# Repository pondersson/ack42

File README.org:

* ACK42

[[file:img/ack42.jpg]]

ACK42 is a DIY sandwich-style keyboard with 42 keys inspired by [[https://zealot.hu/absolem/][Absolem]], [[https://github.com/foostan/crkbd][Corne]] and [[https://blog.splitkb.com/introducing-the-kyria/][Kyria]]. The first prototypes were assembled in September 2020 and they have miraculously survived daily use since then.

This repository is a dump of the artifacts left over from the creation process. Things might be broken, so take this not as a finished product ready to be sent off for manufacturing, but rather as a documented example of one way of creating a keyboard.

I briefly entertained the idea of skipping a PCB and instead 3D-printing wire channels and hand-wiring Kailh hotswap sockets (see [[#gallery][Gallery]]). In the end I went the PCB route and that was a good decision in hindsight. It made assembly much easier and I ended up making 4 versions of the keyboard: 2 MX hotswap versions and 2 Choc low-profile versions, 3 of which I still use regularly, some daily.

** Process (rough)

1) CAD top plate, spending countless hours shifting switch positions around a few millimeters at a time and 3D-printing prototypes until things feel just right
2) CAD everything else: bottom plate, screw holes, MCU cutout and cover
3) Dump top plate to a KiCad-friendly format so the outline and switch positions can be used during PCB design
4) Add all PCB components into KiCad, connect them in the electric schematic and then on the PCB
5) Import top plate into KiCad and painstakingly rotate and position all switch footprints so they're lined up with the top plate
6) Add some art to give the PCB some flair
7) Export Gerber files from KiCad and send them off to the manufacturer
8) Export all necessary SVG files from OpenSCAD, tile them neatly in a single SVG file that represent an acrylic sheet and send it off for laser cutting
9) Order all other necessary components (see [[#materials][Materials]])
10) Wait for parts to arrive
11) Assemble the keyboard(s)
   
**  Materials

All parts required to assemble a single ACK42 keyboard (MX variant):

- 1 ACK42 PCB
- 1 Elite-C microcontroller with pins + stand-offs
- 8 M3 12 mm screws
- 8 M3 cap nuts
- 2 M2 screws
- 2 M2 stand-offs
- 64 0.5 mm washers (or equivalent)
- 42 Kailh hotswap sockets
- 42 through-hole diodes
- 42 MX-style switches
- 42 Keycaps
   
** Gallery

[[file:img/ack42_triangle.jpg]]
[[file:img/ack42_little_pilot.jpg]]
[[file:img/ack42_space_cadet.jpg]]
[[file:img/ack42_low_profile.jpg]]

[[file:img/draft_edge.png]]
[[file:img/draft_handwire.png]]

[[file:img/pcb_render_0.png]]
[[file:img/pcb_render_1.jpg]]
[[file:img/pcb_render_2.png]]
[[file:img/pcb.jpg]]

** License
[[file:LICENSE]] © Pontus Andersson

The KiCad components were taken from the following repositories and their licenses can be found in the corresponding ~pcb~ subdirectories:

- https://github.com/daprice/keyswitches.pretty
- https://github.com/keebio/Keebio-Parts.pretty
- https://github.com/tmk/keyboard_parts.pretty

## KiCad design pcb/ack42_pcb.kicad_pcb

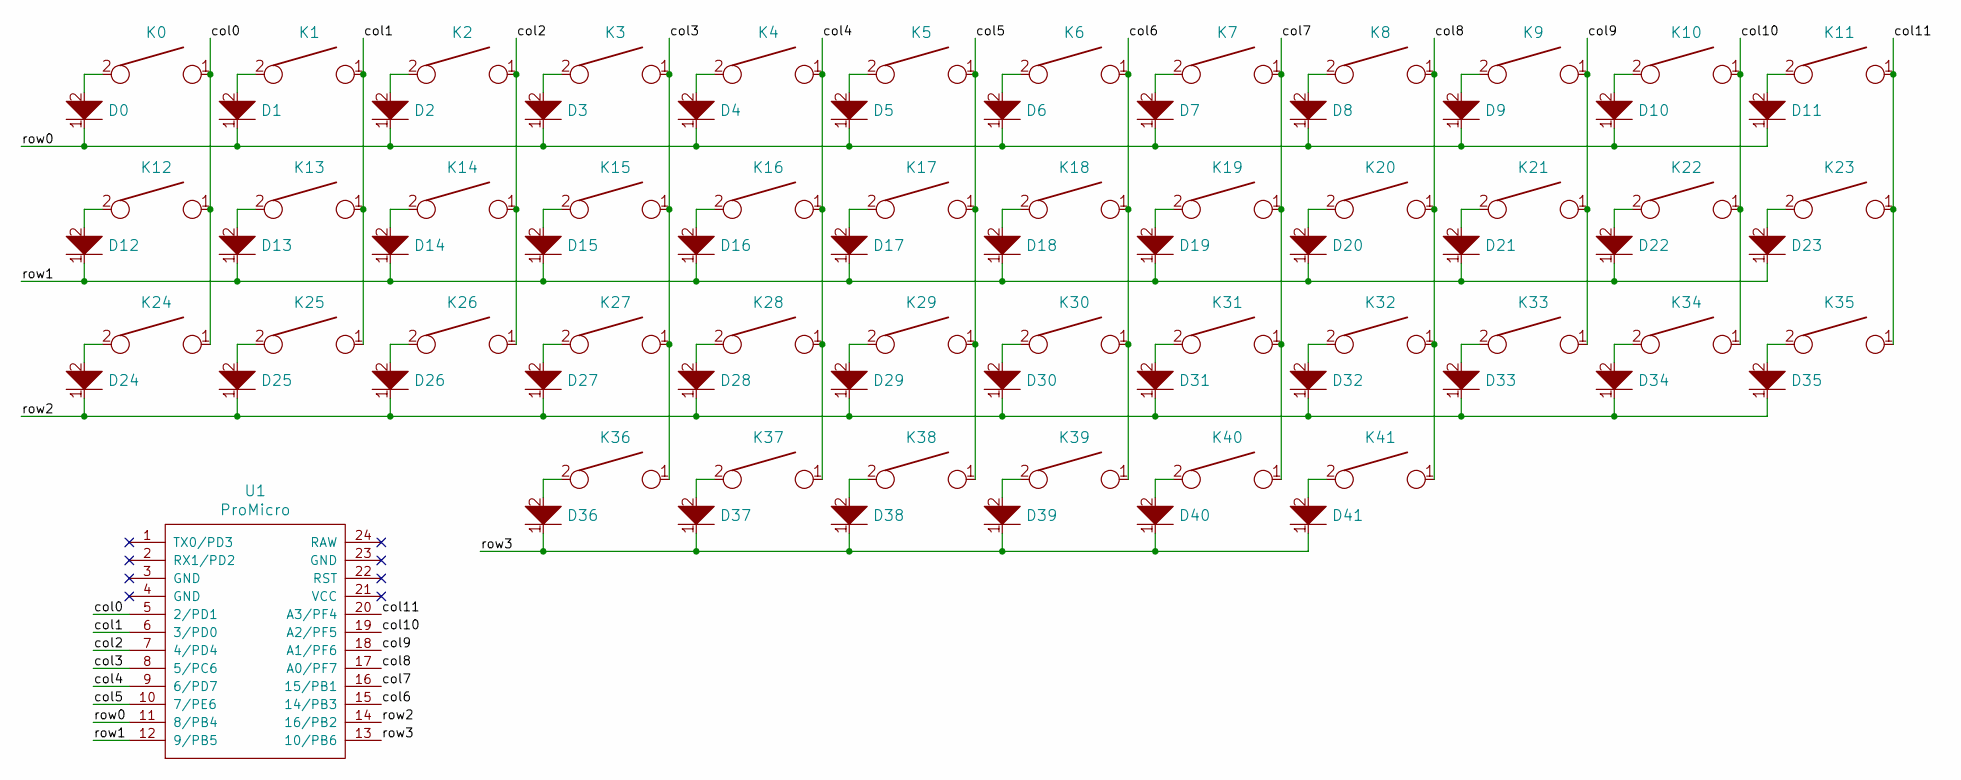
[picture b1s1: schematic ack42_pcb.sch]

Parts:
D0, D1, D2, D3, D4, D5, D6, D7, D8, D9, D10, D11, D12, D13, D14, D15, D16, D17, D18, D19, D20, D21, D22, D23, D24, D25, D26, D27, D28, D29, D30, D31, D32, D33, D34, D35, D36, D37, D38, D39, D40, D41: D; D_SOD123_axial
K0, K1, K2, K3, K4, K5, K6, K7, K8, K9, K10, K11, K12, K13, K14, K15, K16, K17, K18, K19, K20, K21, K22, K23, K24, K25, K26, K27, K28, K29, K30, K31, K32, K33, K34, K35, K36, K37, K38, K39, K40, K41: KEYSW; Kailh_socket_MX1350_optional
U1: ProMicro; ArduinoProMicro-ZigZag

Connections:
/col0: K0.1, K12.1, K24.1, U1.5 (2/PD1)
/col1: K1.1, K13.1, K25.1, U1.6 (3/PD0)
/col2: K2.1, K14.1, K26.1, U1.7 (4/PD4)
/col3: K3.1, K15.1, K27.1, K36.1, U1.8 (5/PC6)
/col4: K4.1, K16.1, K28.1, K37.1, U1.9 (6/PD7)
/col5: K5.1, K17.1, K29.1, K38.1, U1.10 (7/PE6)
/col6: K6.1, K18.1, K30.1, K39.1, U1.15 (14/PB3)
/col7: K7.1, K19.1, K31.1, K40.1, U1.16 (15/PB1)
/col8: K8.1, K20.1, K32.1, K41.1, U1.17 (A0/PF7)
/col9: K9.1, K21.1, K33.1, U1.18 (A1/PF6)
/col10: K10.1, K22.1, K34.1, U1.19 (A2/PF5)
/col11: K11.1, K23.1, K35.1, U1.20 (A3/PF4)
/row0: D0.1, D1.1, D2.1, D3.1, D4.1, D5.1, D6.1, D7.1, D8.1, D9.1, D10.1, D11.1, U1.11 (8/PB4)
/row1: D12.1, D13.1, D14.1, D15.1, D16.1, D17.1, D18.1, D19.1, D20.1, D21.1, D22.1, D23.1, U1.12 (9/PB5)
/row2: D24.1, D25.1, D26.1, D27.1, D28.1, D29.1, D30.1, D31.1, D32.1, D33.1, D34.1, D35.1, U1.14 (16/PB2)
/row3: D36.1, D37.1, D38.1, D39.1, D40.1, D41.1, U1.13 (10/PB6)
unnamed: D0.2, K0.2
unnamed: D1.2, K1.2
unnamed: D2.2, K2.2
unnamed: D3.2, K3.2
unnamed: D4.2, K4.2
unnamed: D5.2, K5.2
unnamed: D6.2, K6.2
unnamed: D7.2, K7.2
unnamed: D8.2, K8.2
unnamed: D9.2, K9.2
unnamed: D10.2, K10.2
unnamed: D11.2, K11.2
unnamed: D12.2, K12.2
unnamed: D13.2, K13.2
unnamed: D14.2, K14.2
unnamed: D15.2, K15.2
unnamed: D16.2, K16.2
unnamed: D17.2, K17.2
unnamed: D18.2, K18.2
unnamed: D19.2, K19.2
unnamed: D20.2, K20.2
unnamed: D21.2, K21.2
unnamed: D22.2, K22.2
unnamed: D23.2, K23.2
unnamed: D24.2, K24.2
unnamed: D25.2, K25.2
unnamed: D26.2, K26.2
unnamed: D27.2, K27.2
unnamed: D28.2, K28.2
unnamed: D29.2, K29.2
unnamed: D30.2, K30.2
unnamed: D31.2, K31.2
unnamed: D32.2, K32.2
unnamed: D33.2, K33.2
unnamed: D34.2, K34.2
unnamed: D35.2, K35.2
unnamed: D36.2, K36.2
unnamed: D37.2, K37.2
unnamed: D38.2, K38.2
unnamed: D39.2, K39.2
unnamed: D40.2, K40.2
unnamed: D41.2, K41.2

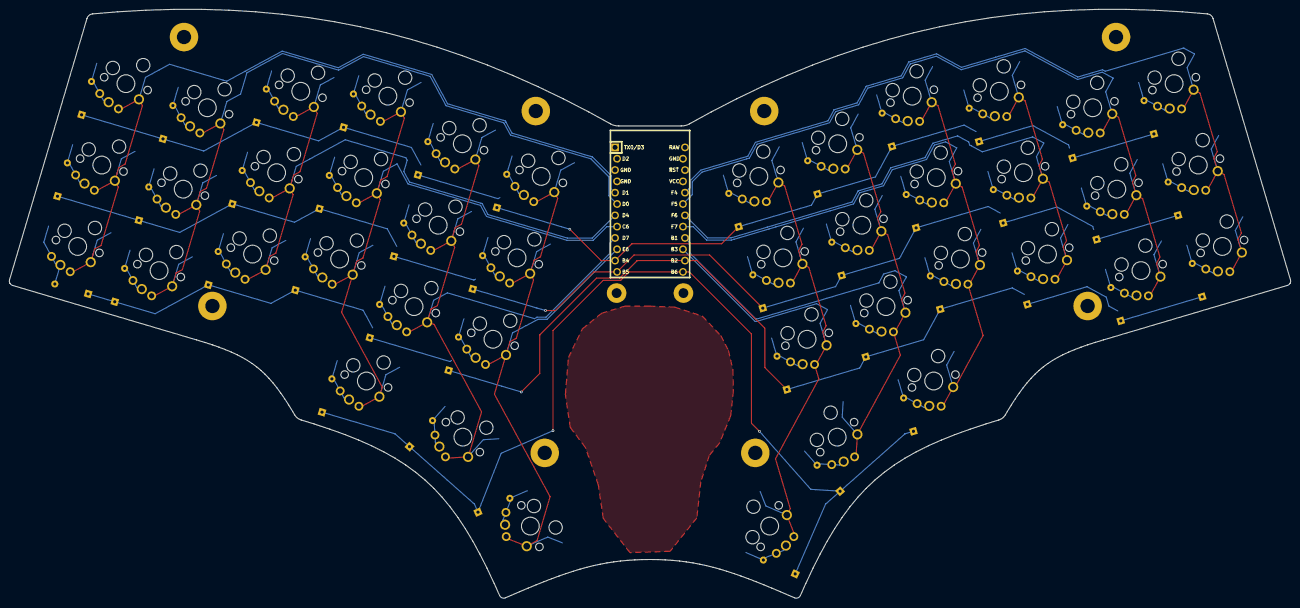
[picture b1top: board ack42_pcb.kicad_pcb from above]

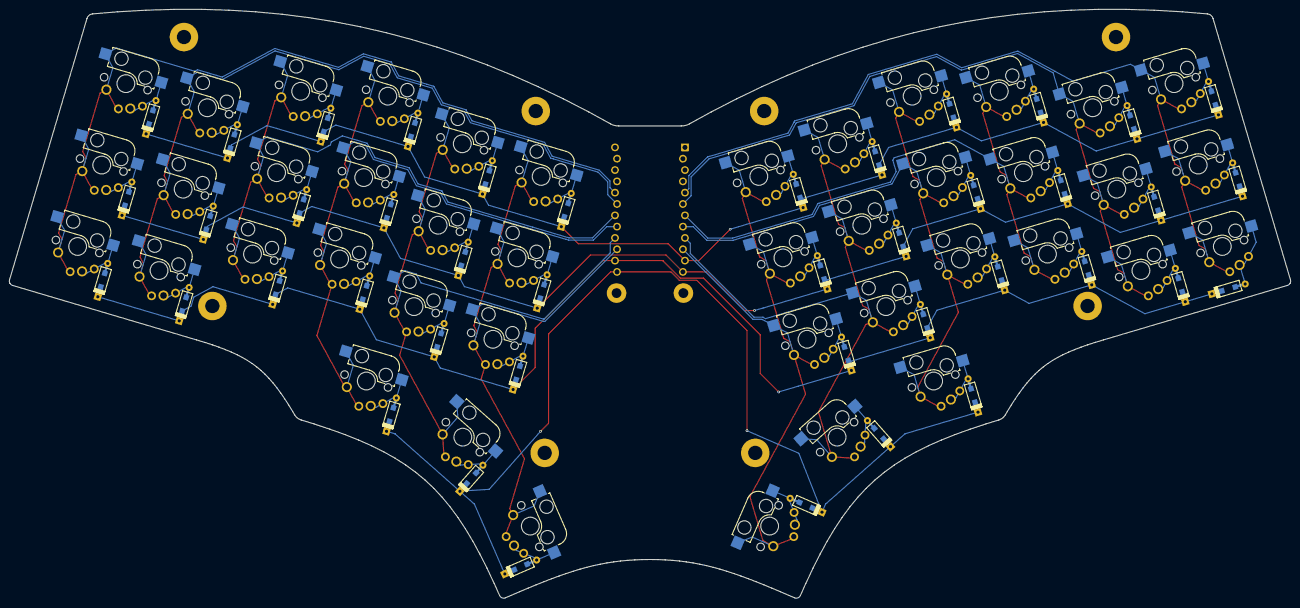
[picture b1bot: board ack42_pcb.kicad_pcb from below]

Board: 2 copper layers, 287.5 x 132.1 mm, 96 parts (42 on the bottom side), 58 nets.

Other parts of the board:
HOLE_M3, HOLE_M3#2: VAL**; HOLE_M2
HOLE_M3#3, HOLE_M3#4, HOLE_M3#5, HOLE_M3#6, HOLE_M3#7, HOLE_M3#8, HOLE_M3#9, HOLE_M3#10: VAL**; HOLE_M3
svg2mod: G***; ack42

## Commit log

2023-07-28 Add files
